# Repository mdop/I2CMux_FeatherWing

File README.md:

# I2CMux FeatherWing

This project is a shield for Adafruits 'Feather' delelopment board series. It is designed to provide 6 STEMMA Qt and 2 STEMMA/STEMMA Qt (or equivalent) I2C outputs which can be set to 2 different voltage levels.

**Suggested Applications**
* Use 5V only sensors with Feather-boards
* Utilize multiple I2C gadgets with same address

**Features**
* Can connect up to 8 I2C gadgets with identical address.
* I2C Channels 0-3 and 4-7 and their respective power can be independently set to voltage levels 3.3V/V_USB/V_BAT
* Channel 1-3 and 5-7 have JST-SH headers compatible with STEMMA Qt and compatible devices without adapter. Channel 0 and 4 can be connected to a JST-PH (STEMMA format) or SH header, both footprints are available.

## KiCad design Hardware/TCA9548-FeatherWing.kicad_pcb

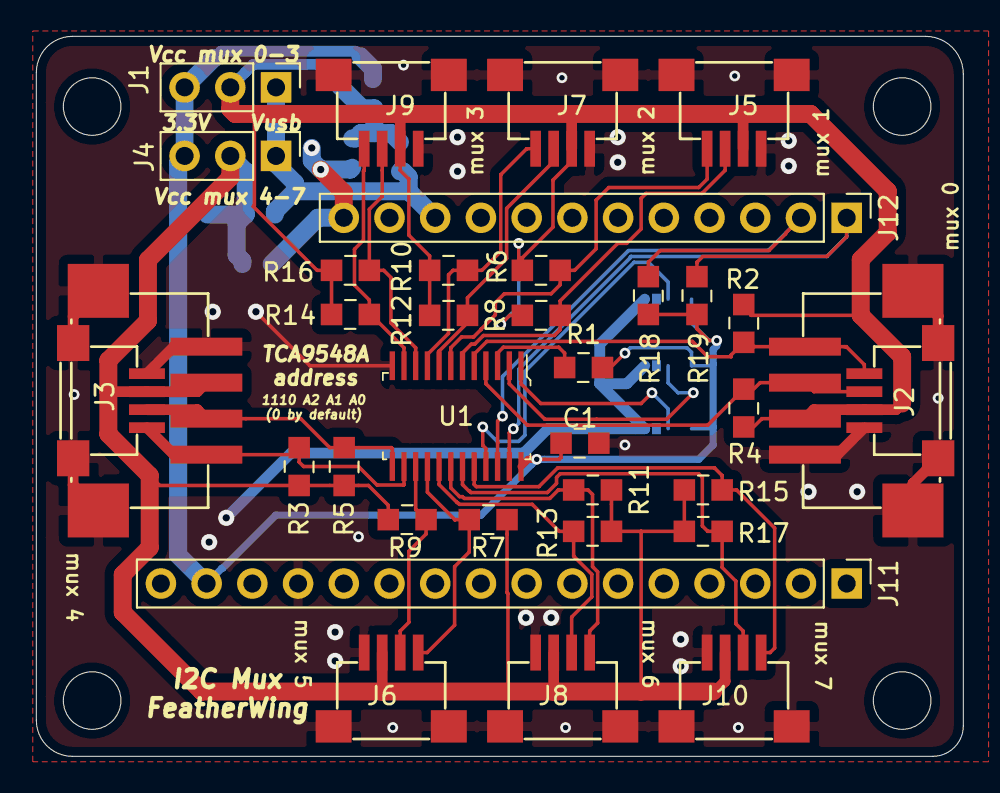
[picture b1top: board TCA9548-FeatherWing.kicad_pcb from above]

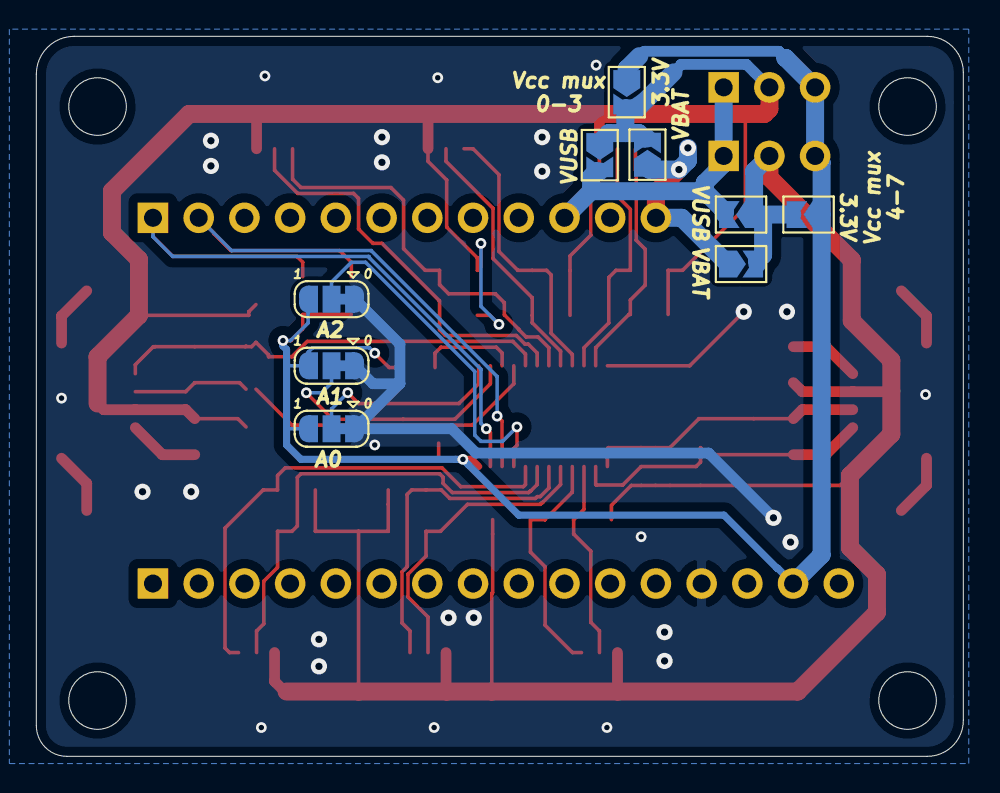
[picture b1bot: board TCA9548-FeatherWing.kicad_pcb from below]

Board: 2 copper layers, 51.5 x 40.0 mm, 46 parts (9 on the bottom side), 28 nets.

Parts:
C1: 1u; 0805
H1, H2, H3, H4: MountingHole; MountingHole_3.2mm_M3_DIN965
J1, J4: Conn_01x03; PinHeader_1x03_P2.54mm_Vertical
J2, J3: JST_PH-SH; JST_PH-SH_4x1
J5, J6, J7, J8, J9, J10: JST_SH; JST_SH_4x1
J11: Conn_01x16; PinHeader_1x16_P2.54mm_Vertical
J12: Conn_01x12; PinHeader_1x12_P2.54mm_Vertical
JP1, JP2, JP3: SolderJumper_3_Bridged12; SolderJumper-3_P1.3mm_Bridged12_RoundedPad1.0x1.5mm
JP4, JP5, JP6, JP7, JP8, JP9: SolderJumper_2_Open; SolderJumper-2_P1.3mm_Open_TrianglePad1.0x1.5mm
R1, R2, R3, R4, R5, R6, R7, R8, R9, R10, R11, R12, R13, R14, R15, R16, R17, R18, R19: 10k; 0805
U1: TCA9548APWR; TSSOP-24_W4.40mm

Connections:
+3V3: C1.1, J1.3, J4.3, J11.15, JP1.3, JP2.3, JP3.3, JP4.1, JP7.1, R1.2, R18.1, R19.1, U1.24
BAT: J12.12, JP6.1, JP9.1
GND: C1.2, J2.0, J2.1, J3.0, J3.1, J5.0, J5.1, J6.0, J6.1, J7.0, J7.1, J8.0, J8.1, J9.0, J9.1, J10.0, J10.1, J11.13, JP1.1, JP2.1, JP3.1, U1.12
I2C_V1: J1.2, J2.2, J5.2, J7.2, J9.2, JP4.2, JP5.1, JP6.2, R2.1, R4.1, R6.1, R8.1, R10.1, R12.1, R14.1, R16.1
I2C_V2: J3.2, J4.2, J6.2, J8.2, J10.2, JP7.2, JP8.1, JP9.2, R3.1, R5.1, R7.1, R9.1, R11.1, R13.1, R15.1, R17.1
unnamed: J2.3, R4.2, U1.4
unnamed: J2.4, R2.2, U1.5
unnamed: J3.3, R5.2, U1.13
unnamed: J3.4, R3.2, U1.14
unnamed: J5.3, R8.2, U1.6
unnamed: J5.4, R6.2, U1.7
unnamed: J6.3, R9.2, U1.15
unnamed: J6.4, R7.2, U1.16
unnamed: J7.3, R12.2, U1.8
unnamed: J7.4, R10.2, U1.9
unnamed: J8.3, R13.2, U1.17
unnamed: J8.4, R11.2, U1.18
unnamed: J9.3, R16.2, U1.10
unnamed: J9.4, R14.2, U1.11
unnamed: J10.3, R17.2, U1.19
unnamed: J10.4, R15.2, U1.20
unnamed: JP1.2, U1.1
unnamed: JP2.2, U1.2
unnamed: JP3.2, U1.21
unnamed: R1.1, U1.3
SCL: J12.2, R18.2, U1.22
SDA: J12.1, R19.2, U1.23
V_USB: J1.1, J4.1, J12.10, JP5.2, JP8.2

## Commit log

2021-01-16 First version of schematic and board
    Also update readme
2021-01-24 Add pullups to source lines
